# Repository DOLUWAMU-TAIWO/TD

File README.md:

# TD
Advanced Embdedded Labs (IOT) AND Hardware Engineering

## Smart Garden Project Motivation

Imagine that you are a busy professional who enjoys gardening but finds it challenging to find the time to give your plants the care they require. You have a variety of plants in your garden, including veggies, herbs, and flowers, and you want to ensure that they are all getting enough water and thriving in the best conditions possible.

You can use your smart garden system to install sensors that monitor the moisture and temperature levels in your garden. These sensors can be linked to an Arduino Uno WiFi Rev 2, which feeds data to a Raspberry Pi 3 that serves as a MQTT broker. The data from the sensors can be used to regulate your water pump, which is also connected to the Raspberry Pi. If the moisture level is too low, for example, the pump can be activated to water the plants.

You may monitor the conditions in your garden in real time using an app on your phone or tablet. You can be notified if the moisture level falls too low or the temperature becomes too hot or cold. You can also create watering plans for your plants to ensure that they get the proper amount of water at the right time of day.

Overall, your smart garden system can save you time and energy while keeping your plants healthy and thriving. It can also provide you with piece of mind because you can watch and control your garden from anywhere at any time.

## PASSWORD-ACTIVATED ALARM SYSTEM

The alarm system project has various use cases and scenarios where it can be applied. One primary use case is residential security. The alarm system can be installed in homes to provide an additional layer of protection against unauthorized access. Users can interact with the system using a keypad connected to the Nexys A7 FPGA, entering security codes to arm or disarm the system. When an intrusion is detected, the system activates the buzzer to generate a loud alarm, alerting occupants and deterring intruders.

Another use case is commercial security. The alarm system can be deployed in commercial buildings, offices, or retail stores to safeguard valuable assets and ensure the safety of employees and customers. Authorized personnel can interact with the system through the keypad, entering access codes to control the system's operation. In the event of a security breach, the system triggers the buzzer to emit a loud alarm, attracting attention and prompting an immediate response from security personnel.

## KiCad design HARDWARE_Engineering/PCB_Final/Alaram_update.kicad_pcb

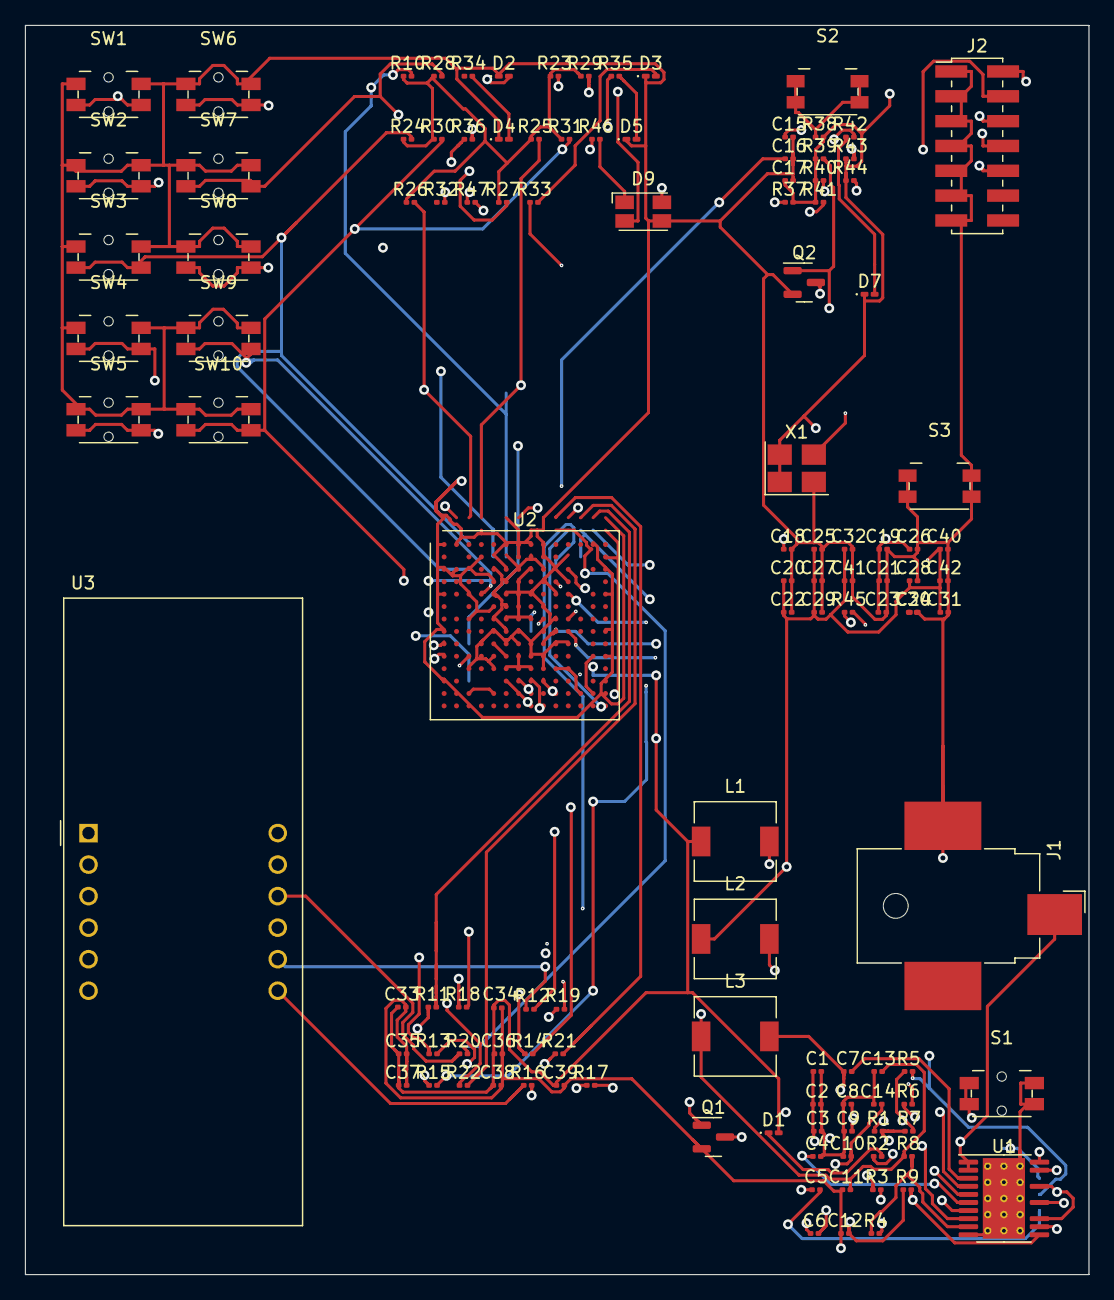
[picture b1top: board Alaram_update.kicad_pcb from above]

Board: 4 copper layers, 85.7 x 100.6 mm, 120 parts (0 on the bottom side), 83 nets.

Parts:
C1, C2: 10 uF; C_0201_0603Metric
C3: C5; C_0201_0603Metric
C4, C7: 1 uF; C_0201_0603Metric
C5, C6, C15, C16, C24: 0.1 uF; C_0201_0603Metric
C8, C9, C10, C11, C12, C13, C14: 22 uF; C_0201_0603Metric
C17, C33: 47uF; C_0201_0603Metric
C18, C20: 47 uF; C_0201_0603Metric
C19, C22, C32, C40, C41: 4.7 uF; C_0201_0603Metric
C21, C23, C25, C26, C27, C28, C29, C30, C31: 0.47 uF; C_0201_0603Metric
C34, C35: 4.7uF; C_0201_0603Metric
C36, C37, C38, C39: 0.47uF; C_0201_0603Metric
C42: 100 uF; C_0201_0603Metric
D1, D2, D3, D4, D5, D7: LED; LED_0201_0603Metric_Pad0.64x0.40mm_HandSolder
D9: LED_RBKG; LED_Avago_PLCC4_3.2x2.8mm_CW
J1: Barrel_Jack_Switch; BarrelJack_CUI_PJ-036AH-SMT_Horizontal
J2: XILINX_JTAG; PinHeader_2x07_P2.00mm_Vertical_SMD
L1, L2, L3: 2.2 uH; L_6.3x6.3_H3
Q1, Q2: DMN2041L; SOT-23
R1, R2, R3: 100K; R_0201_0603Metric
R4, R5, R6: 2.2K; R_0201_0603Metric
R7: 7.36K; R_0201_0603Metric
R8: 3.0K; R_0201_0603Metric
R9, R42: 680; R_0201_0603Metric
R10, R11, R12, R13, R14, R15, R16, R17, R18, R19, R20, R21, R22, R23, R24, R25, R26, R27, R28, R29, R30, R31, R32, R33, R34, R35, R36, R39, R46, R47: 330; R_0201_0603Metric
R37, R38, R45: 4.75K; R_0201_0603Metric
R40, R41, R43, R44: 10K; R_0201_0603Metric
S1: B3FS_1010P; Panasonic_EVQPUL_EVQPUC
S2: CFG_RESET; Panasonic_EVQPUK_EVQPUB
S3: B3FS_1010P; Panasonic_EVQPUK_EVQPUB
SW1: SW_Push_Close; Panasonic_EVQPUL_EVQPUC
SW2, SW3, SW4, SW5, SW6, SW7, SW8, SW9, SW10: SW_Push_close; Panasonic_EVQPUL_EVQPUC
U1: TPS65581; HTSSOP-20-1EP_4.4x6.5mm_P0.65mm_EP3.4x6.5mm_Mask2.75x3.43mm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
U2: XC7S50-FTGB196; Xilinx_FTGB196
U3: CA56-12CGKWA
X1: DSC61XX; Oscillator_SMD_Abracon_ASE-4Pin_3.2x2.5mm_HandSoldering

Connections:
+1V0: C10.2, C12.2, C14.2, C20.1, C22.1, C25.1, C27.1, C28.1, C29.1, C30.1, C31.1, C32.1, C40.1, C41.1, C42.1, L2.1, R9.1, U2.D6 (VCCINT), U2.D8 (VCCINT), U2.E5 (VCCBRAM), U2.E7 (VCCINT), U2.E9 (VCCINT), U2.F6 (VCCINT), U2.G5 (VCCBRAM), U2.G9 (VCCINT), U2.H6 (VCCINT), U2.J5 (VCCBRAM), U2.J9 (VCCINT), U2.K6 (VCCINT), U2.K8 (VCCINT)
+1V8: C11.2, C13.2, C15.1, C18.1, C19.1, C21.1, C23.1, C26.1, L3.1, R8.1, U2.F8 (VCCADC_0), U2.F10 (VCCAUX), U2.H10 (VCCAUX), U2.K10 (VCCAUX), U2.L9 (VCCAUX)
+3.3V: R10.1, R23.1, R24.1, R25.1, R26.1, R27.1, R28.1, R29.1, R30.1, R31.1
+3V3: C8.2, C9.2, C17.1, C24.1, C33.1, C34.1, C35.1, C36.1, C37.1, C38.1, C39.1, D1.2 (A), D7.1 (K), J2.2 (VREF), L1.1, R1.2, R7.1, R37.2, R38.2, R39.1, R40.1, R41.1, R43.1, R44.1, R45.1, U2.G13 (VCCO_14), U2.K13 (VCCO_14), U2.M7 (M0_0), U2.N6 (VCCO_0), U2.N7 (CFGBVS_0), U2.N8 (VCCO_0), U2.N13 (VCCO_14), X1.1 (OE), X1.4 (VCC)
+12V: C1.1, C2.1, C3.1, J1.1, R3.2, U1.1 (VIN), U1.2 (VIN)
/FPGA_JTGA/FPGA_DONE: Q2.1 (G), R39.2, U2.P9 (DONE_0)
/FPGA_JTGA/INIT_B: R37.1, U2.P8 (INIT_B_0)
/FPGA_JTGA/JTAG_TCK: J2.6 (TCK), R41.2, U2.A7 (TCK_0)
/FPGA_JTGA/JTAG_TDI: J2.10 (TDI), R44.2, U2.P6 (TDO_0)
/FPGA_JTGA/JTAG_TDO: J2.8 (TDO), R43.2, U2.P7 (TDI_0)
/FPGA_JTGA/JTAG_TMS: J2.4 (TMS), R40.2, U2.M6 (TMS_0)
/FPGA_JTGA/PROGRAM_B: R38.1, S2.1, S2.2, U2.L7 (PROGRAM_B_0)
/FPGA_key/SW3_R: R24.2, SW3.2 (B), U2.C3 (IO_L1N_T0_34)
/FPGA_key/SW4_R: R25.2, SW4.2 (B), U2.A4 (IO_L2P_T0_34)
/FPGA_key/SW5_R: R26.2, SW5.2 (B), U2.A3 (IO_L2N_T0_34)
/FPGA_key/SW6_R: R27.2, SW6.2 (B), U2.B3 (IO_L3P_T0_DQS_34)
/FPGA_key/SW7_R: R28.2, SW7.2 (B), U2.A2 (IO_L3N_T0_DQS_34)
/FPGA_key/SW8_R: R29.2, SW8.2 (B), U2.B5 (IO_L4P_T0_34)
/FPGA_key/SW9_R: SW9.2 (B), U2.G4 (IO_L12P_T1_MRCC_34)
/FPGA_key/SW10_R: R30.2, R31.2, SW10.2 (B), U2.H3 (IO_L13N_T2_MRCC_34)
/power/PG00D: Q1.1 (G), R1.1, U1.7 (PG)
/power/SW1: C7.1, L3.2, U1.4 (SW1)
/power/SW2: C6.1, L2.2, U1.19 (SW2)
/power/SW3: C5.1, L1.2, U1.15 (SW3)
GND: C1.2, C2.2, C3.2, C4.2, C8.1, C9.1, C10.1, C11.1, C12.1, C13.1, C14.1, C15.2, C16.2, C17.2, C18.2, C19.2, C20.2, C21.2, C22.2, C23.2, C24.2, C25.2, C26.2, C27.2, C28.2, C29.2, C30.2, C31.2, C32.2, C33.2, C34.2, C35.2, C36.2, C37.2, C38.2, C39.2, C40.2, C41.2, C42.2, D2.1 (K), D3.1 (K), D4.1 (K), D5.1 (K), D9.3 (K), J1.2, J2.1 (GND), J2.3 (GND), J2.5 (GND), J2.7 (GND), J2.9 (GND), J2.11 (GND), J2.13 (GND), Q1.2 (S), Q2.2 (S), S1.1, S1.2, S3.1, S3.2, SW1.1 (A), SW2.1 (A), SW3.1 (A), SW4.1 (A), SW5.1 (A), SW6.1 (A), SW7.1 (A), SW8.1 (A), SW9.1 (A), SW10.1 (A), U1.10 (GND), U1.21 (PAD), U2.A1 (GND), U2.A6 (GND), U2.A9 (GND), U2.A11 (GND), U2.A14 (GND), U2.B4 (GND), U2.B7 (GND), U2.B8 (VCCBATT_0), U2.B9 (GND), U2.C2 (GND), U2.C6 (GND), U2.C7 (GND), U2.C8 (GND), U2.C9 (GND), U2.C13 (GND), U2.D5 (GND), U2.D7 (GND), U2.D9 (GND), U2.D11 (GND), U2.E1 (GND), U2.E3 (GND), U2.E6 (GND), U2.E8 (GND), U2.E10 (GND), U2.E14 (GND), U2.F5 (GND), U2.F7 (GNDADC_0), U2.F9 (GND), U2.G3 (GND), U2.G6 (GND), U2.G7 (VREFN_0), U2.G8 (VP_0), U2.G10 (GND), U2.G12 (GND), U2.H5 (GND), U2.H7 (VN_0), U2.H9 (GND), U2.J6 (GND), U2.J7 (DXN_0), U2.J8 (DXP_0), U2.J10 (GND), U2.K1 (GND), U2.K5 (GND), U2.K7 (GND), U2.K9 (GND), U2.K14 (GND), U2.L4 (GND), U2.L6 (GND), U2.L8 (GND), U2.L10 (GND), U2.L11 (GND), U2.M8 (M1_0), U2.M9 (M2_0), U2.N3 (GND), U2.N5 (GND), U2.N9 (GND), U2.N12 (GND), U2.P1 (GND), U2.P14 (GND), X1.2 (GND)
unnamed: D1.1 (K), R2.2
unnamed: D2.2 (A), R32.2
unnamed: D3.2 (A), R33.2
unnamed: D4.2 (A), R34.2
unnamed: D5.2 (A), R35.2
unnamed: D7.2 (A), R42.1
unnamed: D9.2 (BA), R47.2
unnamed: D9.4 (GA), R36.2
unnamed: D9.1 (RA), R46.2
unnamed: Q1.3 (D), R2.1
unnamed: Q2.3 (D), R42.2
unnamed: R10.2, SW1.2 (B), U2.B6 (IO_0_34)
unnamed: R23.2, SW2.2 (B), U2.D3 (IO_L1P_T0_34)
unnamed: R3.1, U1.8 (EN1), U1.13 (EN3), U1.17 (EN2)
unnamed: R4.2, U1.5 (PGND1)
unnamed: R6.2, U1.18 (PGND2)
unnamed: R5.2, U1.16 (PGND3)
unnamed: C7.2, U1.3 (VBST1)
unnamed: C6.2, U1.20 (VBST2)
unnamed: C5.2, U1.14 (VBST3)
unnamed: R4.1, R8.2, U1.9 (VFB1)
unnamed: R6.1, R9.2, U1.11 (VFB2)
unnamed: R5.1, R7.2, U1.12 (VFB3)
unnamed: C4.1, U1.6 (VREG5)
unnamed: R15.2, U2.E11 (IO_0_14)
unnamed: R17.2, U2.B12 (IO_L1N_T0_D01_DIN_14)
unnamed: R16.2, U2.B11 (IO_L1P_T0_D00_MOSI_14)
unnamed: R19.2, U2.C10 (IO_L2N_T0_D03_14)
unnamed: R18.2, U2.D10 (IO_L2P_T0_D02_14)
unnamed: R21.2, U2.A10 (IO_L3N_T0_DQS_EMCCLK_14)
unnamed: R20.2, U2.B10 (IO_L3P_T0_DQS_PUDC_B_14)
unnamed: R11.2, U2.A13 (IO_L4N_T0_D05_14)
unnamed: R22.2, U2.A12 (IO_L4P_T0_D04_14)
unnamed: R13.2, U2.B14 (IO_L5N_T0_D07_14)
unnamed: R12.2, U2.B13 (IO_L5P_T0_D06_14)
unnamed: R14.2, U2.C11 (IO_L6P_T0_FCS_B_14)
unnamed: R33.1, U2.K3 (IO_L16N_T2_34)
unnamed: R32.1, U2.K4 (IO_L16P_T2_34)
unnamed: R35.1, U2.J3 (IO_L17N_T2_34)
unnamed: R34.1, U2.J4 (IO_L17P_T2_34)
unnamed: R36.1, U2.L1 (IO_L18N_T2_34)
unnamed: R46.1, U2.M1 (IO_L18P_T2_34)
unnamed: R47.1, U2.M3 (IO_L19P_T3_34)
unnamed: C16.1, U2.H8 (VREFP_0)
unnamed: R14.1, U3.12 (CA1)
unnamed: R13.1, U3.9 (CA2)
unnamed: R12.1, U3.8 (CA3)
unnamed: R11.1, U3.6 (CA4)
unnamed: R22.1, U3.3 (DPX)
unnamed: R15.1, U3.11 (a)
unnamed: R16.1, U3.7 (b)
unnamed: R17.1, U3.4 (c)
unnamed: R18.1, U3.2 (d)
unnamed: R19.1, U3.1 (e)
unnamed: R20.1, U3.10 (f)
unnamed: R21.1, U3.5 (g)
SYSCLK: U2.G11 (IO_L12P_T1_MRCC_14), X1.3 (OUT)
SYSRES: R45.2, U2.H11 (IO_L13P_T2_MRCC_14)

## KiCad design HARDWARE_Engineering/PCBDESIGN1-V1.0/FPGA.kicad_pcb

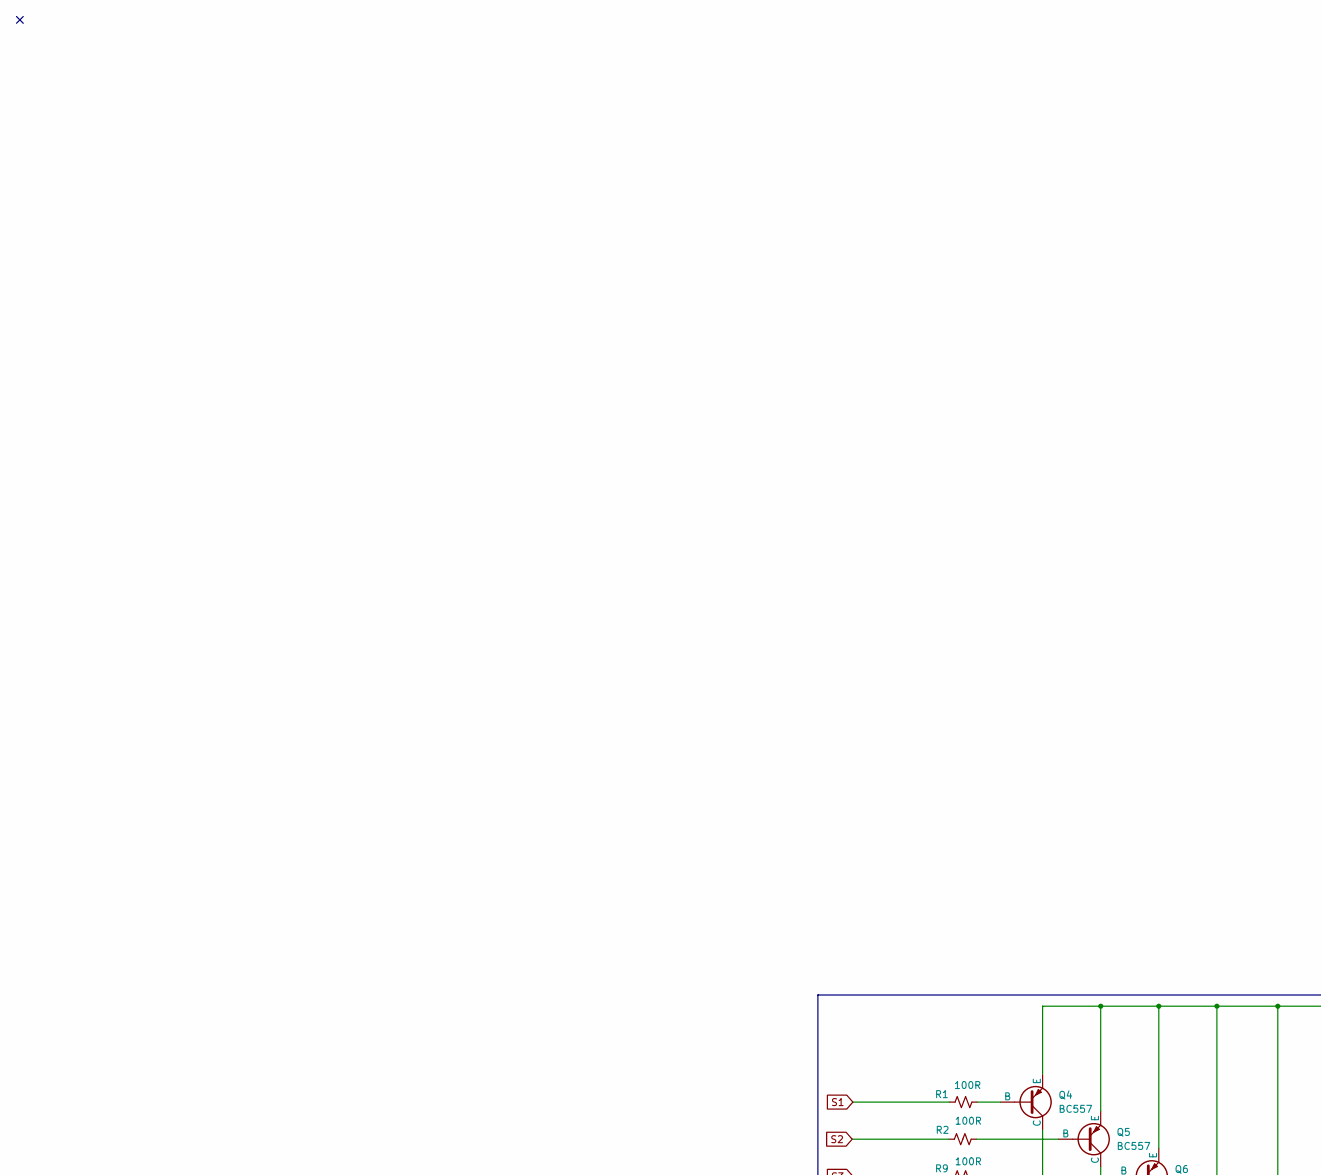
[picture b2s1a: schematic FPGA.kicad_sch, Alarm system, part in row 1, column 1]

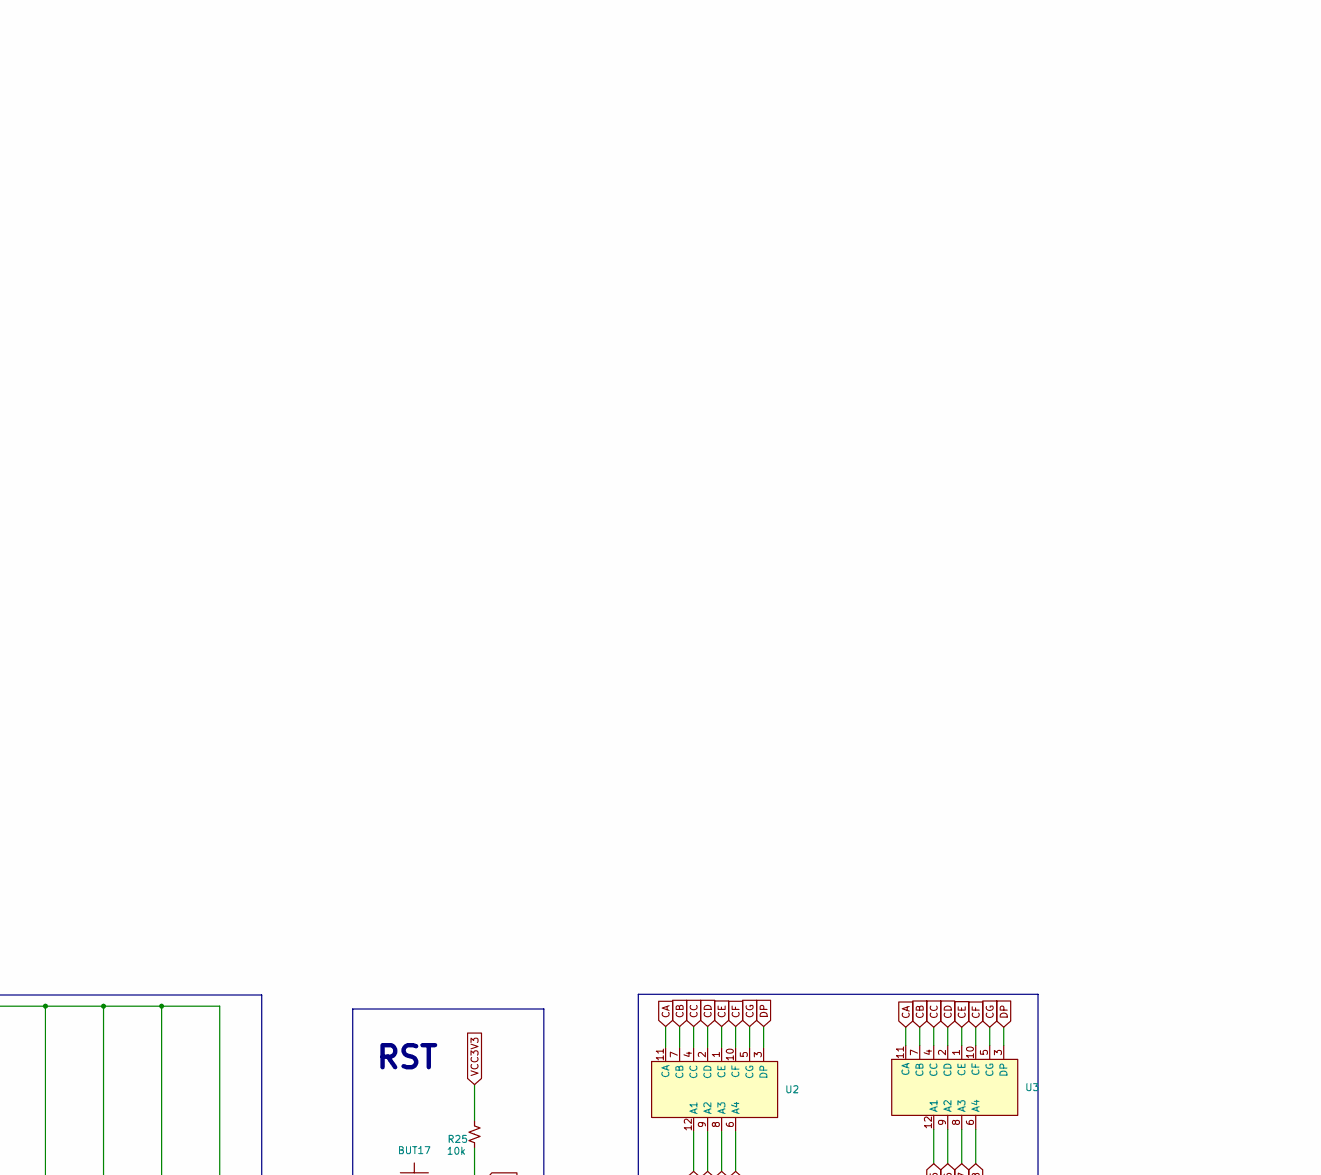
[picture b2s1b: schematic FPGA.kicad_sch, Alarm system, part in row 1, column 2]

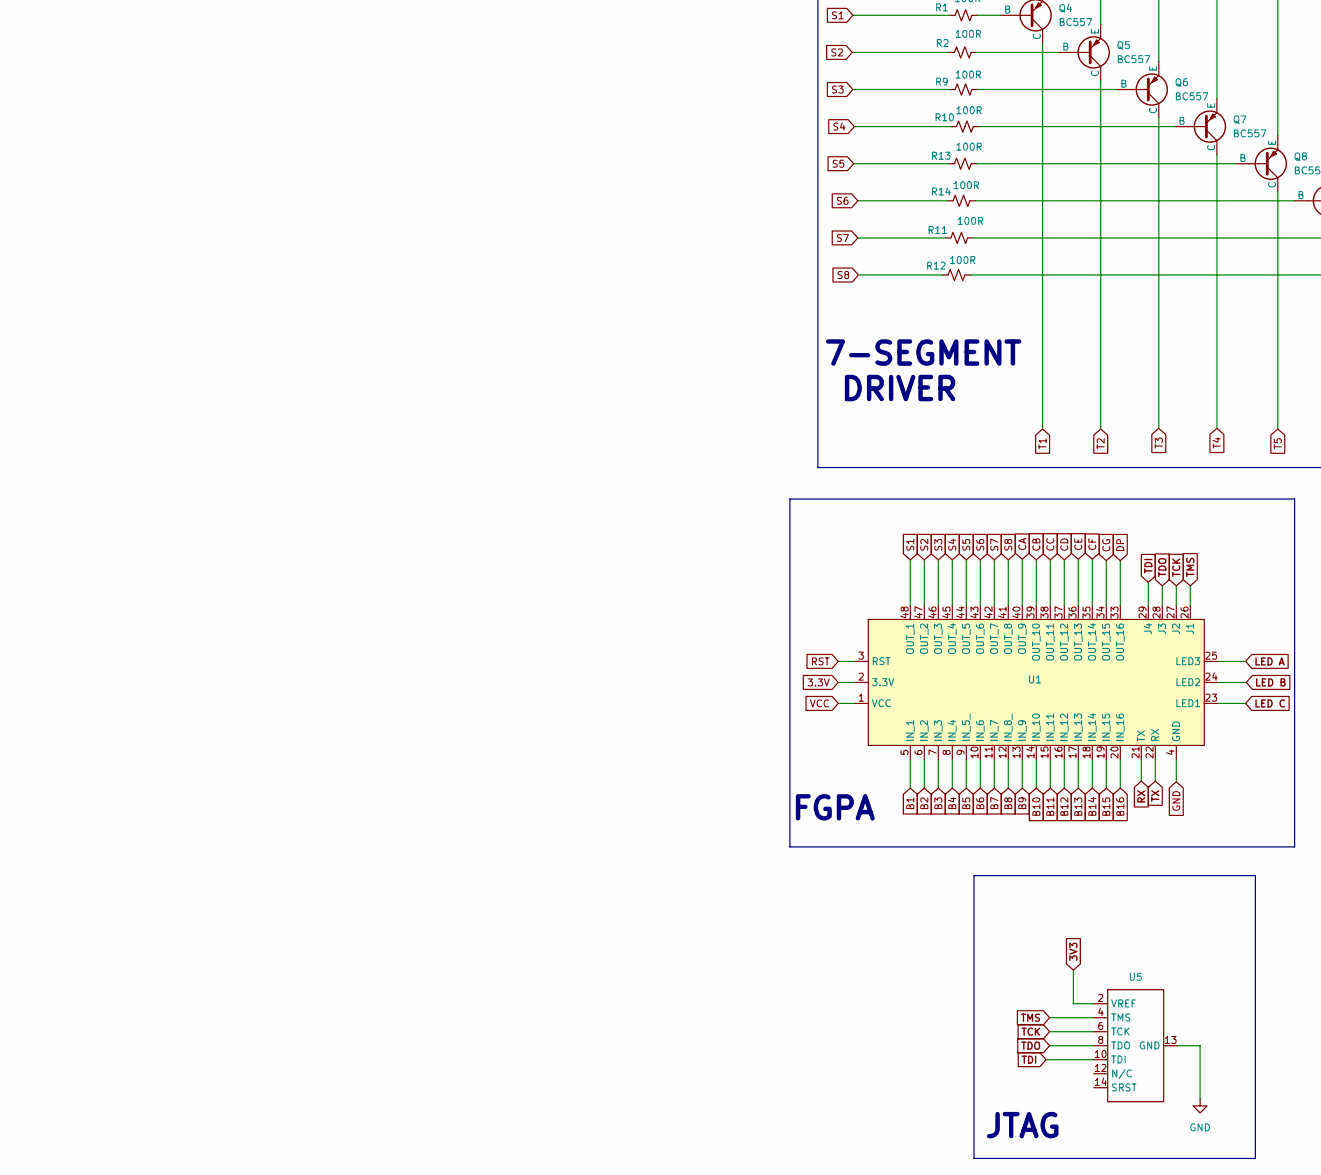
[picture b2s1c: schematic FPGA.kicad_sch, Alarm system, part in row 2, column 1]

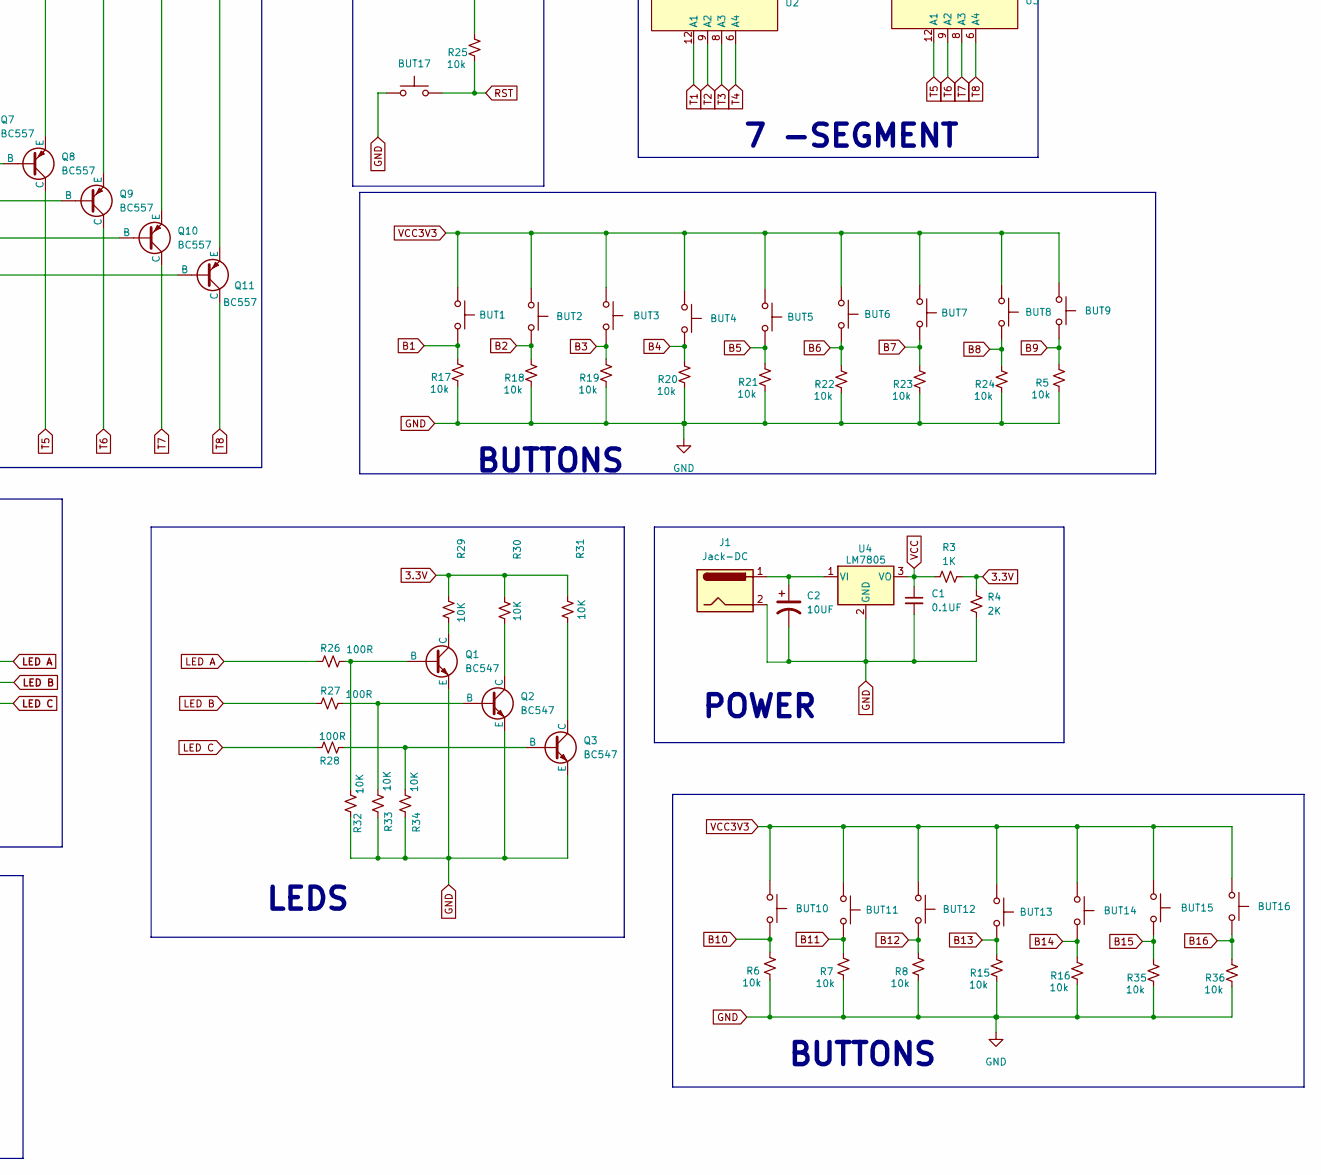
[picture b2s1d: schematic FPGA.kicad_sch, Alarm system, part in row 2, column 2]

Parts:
BUT1, BUT2, BUT3, BUT4, BUT5, BUT6, BUT7, BUT8, BUT9, BUT10, BUT11, BUT12, BUT13, BUT14, BUT15, BUT16, BUT17: SW_Push; SW_Cherry_MX_1.00u_PCB
C1: 0.1UF; C_Axial_L5.1mm_D3.1mm_P7.50mm_Horizontal
C2: 10UF; C_Radial_D5.0mm_H5.0mm_P2.00mm
J1: Jack-DC; BarrelJack_Horizontal
Q1, Q2, Q3: BC547; TO-92_Inline
Q4, Q5, Q6, Q7, Q8, Q9, Q10, Q11: BC557; TO-92_Inline
R1, R2, R9, R10, R11, R12, R13, R14, R26, R27, R28: 100R; R_Axial_DIN0207_L6.3mm_D2.5mm_P7.62mm_Horizontal
R3: 1K; R_Axial_DIN0207_L6.3mm_D2.5mm_P7.62mm_Horizontal
R4: 2K; R_Axial_DIN0207_L6.3mm_D2.5mm_P7.62mm_Horizontal
R5, R6, R7, R8, R15, R16, R17, R18, R19, R20, R21, R22, R23, R24, R25, R35, R36: 10k; R_Axial_DIN0207_L6.3mm_D2.5mm_P7.62mm_Horizontal
R29, R30, R31, R32, R33, R34: 10K; R_Axial_DIN0207_L6.3mm_D2.5mm_P7.62mm_Horizontal
U1: DIP-48_W15.24mm_LongPads
U2, U3: KW4-281A seven segment
U4: LM7805; TO-220-3_Vertical
U5: (no value)

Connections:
3.3V: R3.2, R4.1, R29.2, R30.2, R31.2, U1.2 (3.3V)
3V3: U5.2 (VREF)
B1: BUT1.2, R17.2, U1.5 (IN_1)
B2: BUT2.2, R18.2, U1.6 (IN_2)
B3: BUT3.2, R19.2, U1.7 (IN_3)
B4: BUT4.2, R20.2, U1.8 (IN_4)
B5: BUT5.2, R21.2, U1.9 (IN_5_)
B6: BUT6.2, R22.2, U1.10 (IN_6)
B7: BUT7.2, R23.2, U1.11 (IN_7)
B8: BUT8.2, R24.2, U1.12 (IN_8_)
B9: BUT9.2, R5.2, U1.13 (IN_9)
B10: BUT10.2, R6.2, U1.14 (IN_10)
B11: BUT11.2, R7.2, U1.15 (IN_11)
B12: BUT12.2, R8.2, U1.16 (IN_12)
B13: BUT13.2, R15.2, U1.17 (IN_13)
B14: BUT14.2, R16.2, U1.18 (IN_14)
B15: BUT15.2, R35.2, U1.19 (IN_15)
B16: BUT16.2, R36.2, U1.20 (IN_16)
CA: U1.40 (OUT_9), U2.11 (CA), U3.11 (CA)
CB: U1.39 (OUT_10), U2.7 (CB), U3.7 (CB)
CC: U1.38 (OUT_11), U2.4 (CC), U3.4 (CC)
CD: U1.37 (OUT_12), U2.2 (CD), U3.2 (CD)
CE: U1.36 (OUT_13), U2.1 (CE), U3.1 (CE)
CF: U1.35 (OUT_14), U2.10 (CF), U3.10 (CF)
CG: U1.34 (OUT_15), U2.5 (CG), U3.5 (CG)
DP: U1.33 (OUT_16), U2.3 (DP), U3.3 (DP)
GND: BUT17.1, C1.2, C2.2, J1.2, Q1.3 (E), Q2.3 (E), Q3.3 (E), R4.2, R5.1, R6.1, R7.1, R8.1, R15.1, R16.1, R17.1, R18.1, R19.1, R20.1, R21.1, R22.1, R23.1, R24.1, R32.1, R33.1, R34.1, R35.1, R36.1, U1.4 (GND), U4.2 (GND), U5.13 (GND)
LED A: R26.2, U1.25 (LED3)
LED B: R27.2, U1.24 (LED2)
LED C: R28.2, U1.23 (LED1)
unnamed: Q1.2 (B), R26.1, R32.2
unnamed: Q1.1 (C), R29.1
unnamed: Q2.2 (B), R27.1, R33.2
unnamed: Q2.1 (C), R30.1
unnamed: Q3.2 (B), R28.1, R34.2
unnamed: Q3.1 (C), R31.1
unnamed: Q4.2 (B), R1.2
unnamed: Q5.2 (B), R2.2
unnamed: Q6.2 (B), R9.2
unnamed: Q7.2 (B), R10.2
unnamed: Q8.2 (B), R13.2
unnamed: Q9.2 (B), R14.2
unnamed: Q10.2 (B), R11.2
unnamed: Q4.3 (E), Q5.3 (E), Q6.3 (E), Q7.3 (E), Q8.3 (E), Q9.3 (E), Q10.3 (E), Q11.3 (E)
unnamed: Q11.2 (B), R12.2
unnamed: C2.1, J1.1, U4.1 (VI)
RST: BUT17.2, R25.1, U1.3 (RST)
RX: U1.21 (TX)
S1: R1.1, U1.48 (OUT_1)
S2: R2.1, U1.47 (OUT_2)
S3: R9.1, U1.46 (OUT_3)
S4: R10.1, U1.45 (OUT_4)
S5: R13.1, U1.44 (OUT_5)
S6: R14.1, U1.43 (OUT_6)
S7: R11.1, U1.42 (OUT_7)
S8: R12.1, U1.41 (OUT_8)
T1: Q4.1 (C), U2.12 (A1)
T2: Q5.1 (C), U2.9 (A2)
T3: Q6.1 (C), U2.8 (A3)
T4: Q7.1 (C), U2.6 (A4)
T5: Q8.1 (C), U3.12 (A1)
T6: Q9.1 (C), U3.9 (A2)
T7: Q10.1 (C), U3.8 (A3)
T8: Q11.1 (C), U3.6 (A4)
TCK: U1.27 (J2), U5.6 (TCK)
TDI: U1.29 (J4), U5.10 (TDI)
TDO: U1.28 (J3), U5.8 (TDO)
TMS: U1.26 (J1), U5.4 (TMS)
TX: U1.22 (RX)
VCC: C1.1, R3.1, U1.1 (VCC), U4.3 (VO)
VCC3V3: BUT1.1, BUT2.1, BUT3.1, BUT4.1, BUT5.1, BUT6.1, BUT7.1, BUT8.1, BUT9.1, BUT10.1, BUT11.1, BUT12.1, BUT13.1, BUT14.1, BUT15.1, BUT16.1, R25.2

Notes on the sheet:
POWER
7-SEGMENT DRIVER
7 -SEGMENT
JTAG
BUTTONS
FGPA
LEDS
RST

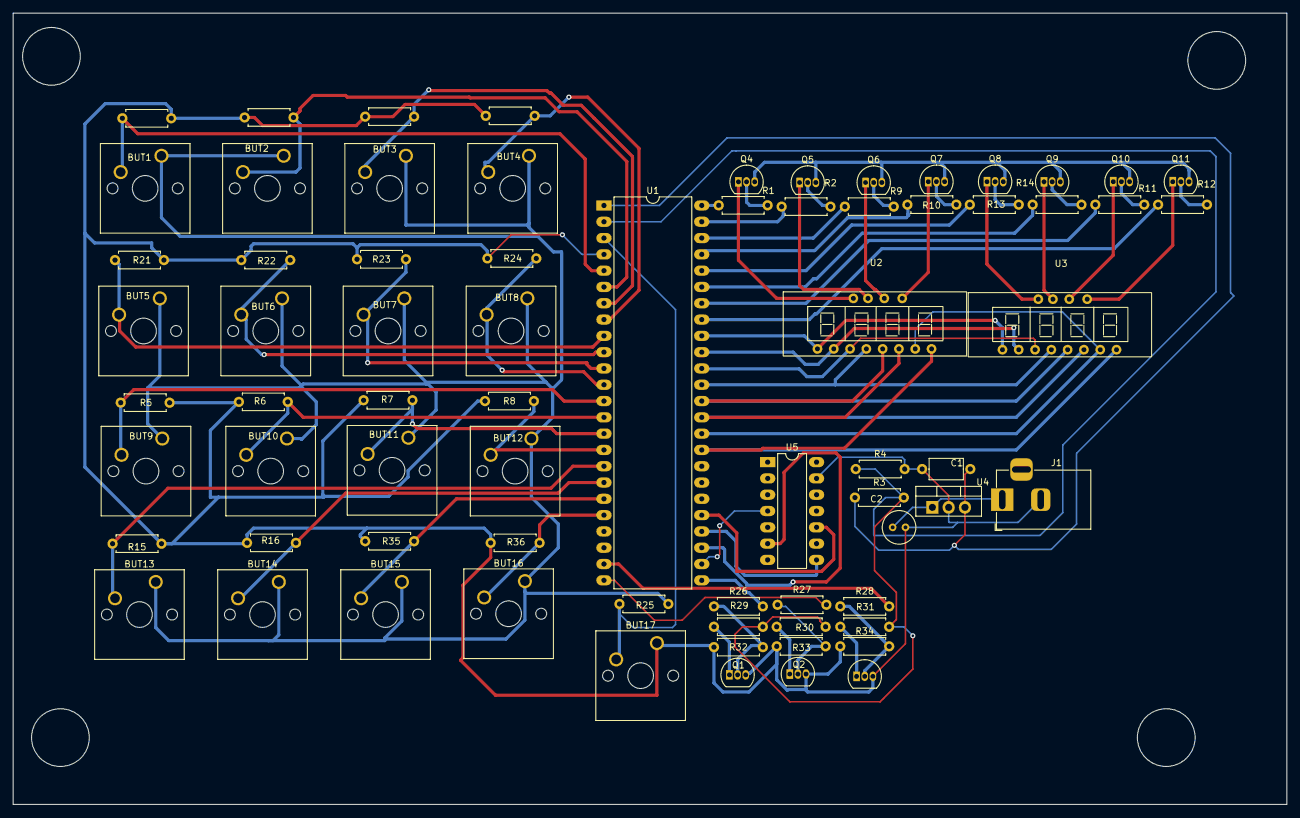
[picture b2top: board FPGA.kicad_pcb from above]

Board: 2 copper layers, 198.5 x 123.3 mm, 72 parts (0 on the bottom side), 68 nets.

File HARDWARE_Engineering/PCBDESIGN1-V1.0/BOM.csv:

"Source:","C:\Users\doluwamu.kaye\Desktop\alarm system\FPGA final\FPGA.kicad_sch"
"Date:","16/06/2023 23:28:07"
"Tool:","Eeschema 7.0.2"
"Generator:","C:\Program Files\KiCad\7.0\bin\scripting\plugins/bom_csv_grouped_by_value_with_fp.py"
"Component Count:","72"
"Ref","Qnty","Value","Cmp name","Footprint","Description","Vendor","DNP"
"BUT1, BUT2, BUT3, BUT4, BUT5, BUT6, BUT7, BUT8, BUT9, BUT10, BUT11, BUT12, BUT13, BUT14, BUT15, BUT16, BUT17","17","SW_Push","SW_Push","Button_Switch_Keyboard:SW_Cherry_MX_1.00u_PCB","Push button switch, generic, two pins","",""
"C1","1","0.1UF","C_Small","Capacitor_THT:C_Axial_L5.1mm_D3.1mm_P7.50mm_Horizontal","Unpolarized capacitor, small symbol","",""
"C2","1","10UF","C_Polarized_US","Capacitor_THT:C_Radial_D5.0mm_H5.0mm_P2.00mm","Polarized capacitor, US symbol","",""
"J1","1","Jack-DC","Jack-DC","Connector_BarrelJack:BarrelJack_Horizontal","DC Barrel Jack","",""
"Q1, Q2, Q3","3","BC547","NPN","Package_TO_SOT_THT:TO-92_Inline","Bipolar transistor symbol for simulation only, substrate tied to the emitter","",""
"Q4, Q5, Q6, Q7, Q8, Q9, Q10, Q11","8","BC557","PNP","Package_TO_SOT_THT:TO-92_Inline","Bipolar transistor symbol for simulation only, substrate tied to the emitter","",""
"R1, R2, R9, R10, R11, R12, R13, R14, R26, R27, R28","11","100R","R_Small_US","Resistor_THT:R_Axial_DIN0207_L6.3mm_D2.5mm_P7.62mm_Horizontal","Resistor, small US symbol","",""
"R3","1","1K","R_Small_US","Resistor_THT:R_Axial_DIN0207_L6.3mm_D2.5mm_P7.62mm_Horizontal","Resistor, small US symbol","",""
"R4","1","2K","R_Small_US","Resistor_THT:R_Axial_DIN0207_L6.3mm_D2.5mm_P7.62mm_Horizontal","Resistor, small US symbol","",""
"R5, R6, R7, R8, R15, R16, R17, R18, R19, R20, R21, R22, R23, R24, R25, R35, R36","17","10k","R_Small_US","Resistor_THT:R_Axial_DIN0207_L6.3mm_D2.5mm_P7.62mm_Horizontal","Resistor, small US symbol","",""
"R29, R30, R31, R32, R33, R34","6","10K","R_Small_US","Resistor_THT:R_Axial_DIN0207_L6.3mm_D2.5mm_P7.62mm_Horizontal","Resistor, small US symbol","",""
"U1","1","~","myFGPA","Package_DIP:DIP-48_W15.24mm_LongPads","","",""
"U2, U3","2","~","KW4-281A","myCustomFootprints:KW4-281A seven segment","","",""
"U4","1","LM7805","LM7805_TO220","Package_TO_SOT_THT:TO-220-3_Vertical","Positive 1A 35V Linear Regulator, Fixed Output 5V, TO-220","",""
"U5","1","~","myJTAG","","","",""

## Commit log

2023-05-11 Create LAB!:MD
2023-05-11 IOT.md
2023-05-11 Create Lab 1.
2023-05-11 Create Lab 1.md
    Creation of Half adder and Full Adder, made use of components , Also test bench.
2023-05-12 Create Half adder
2023-05-12 Create Concept_Draft
2023-06-16 Create PCB Schematics and Layout
2023-06-17 Create ALARM SYSTEM Files
